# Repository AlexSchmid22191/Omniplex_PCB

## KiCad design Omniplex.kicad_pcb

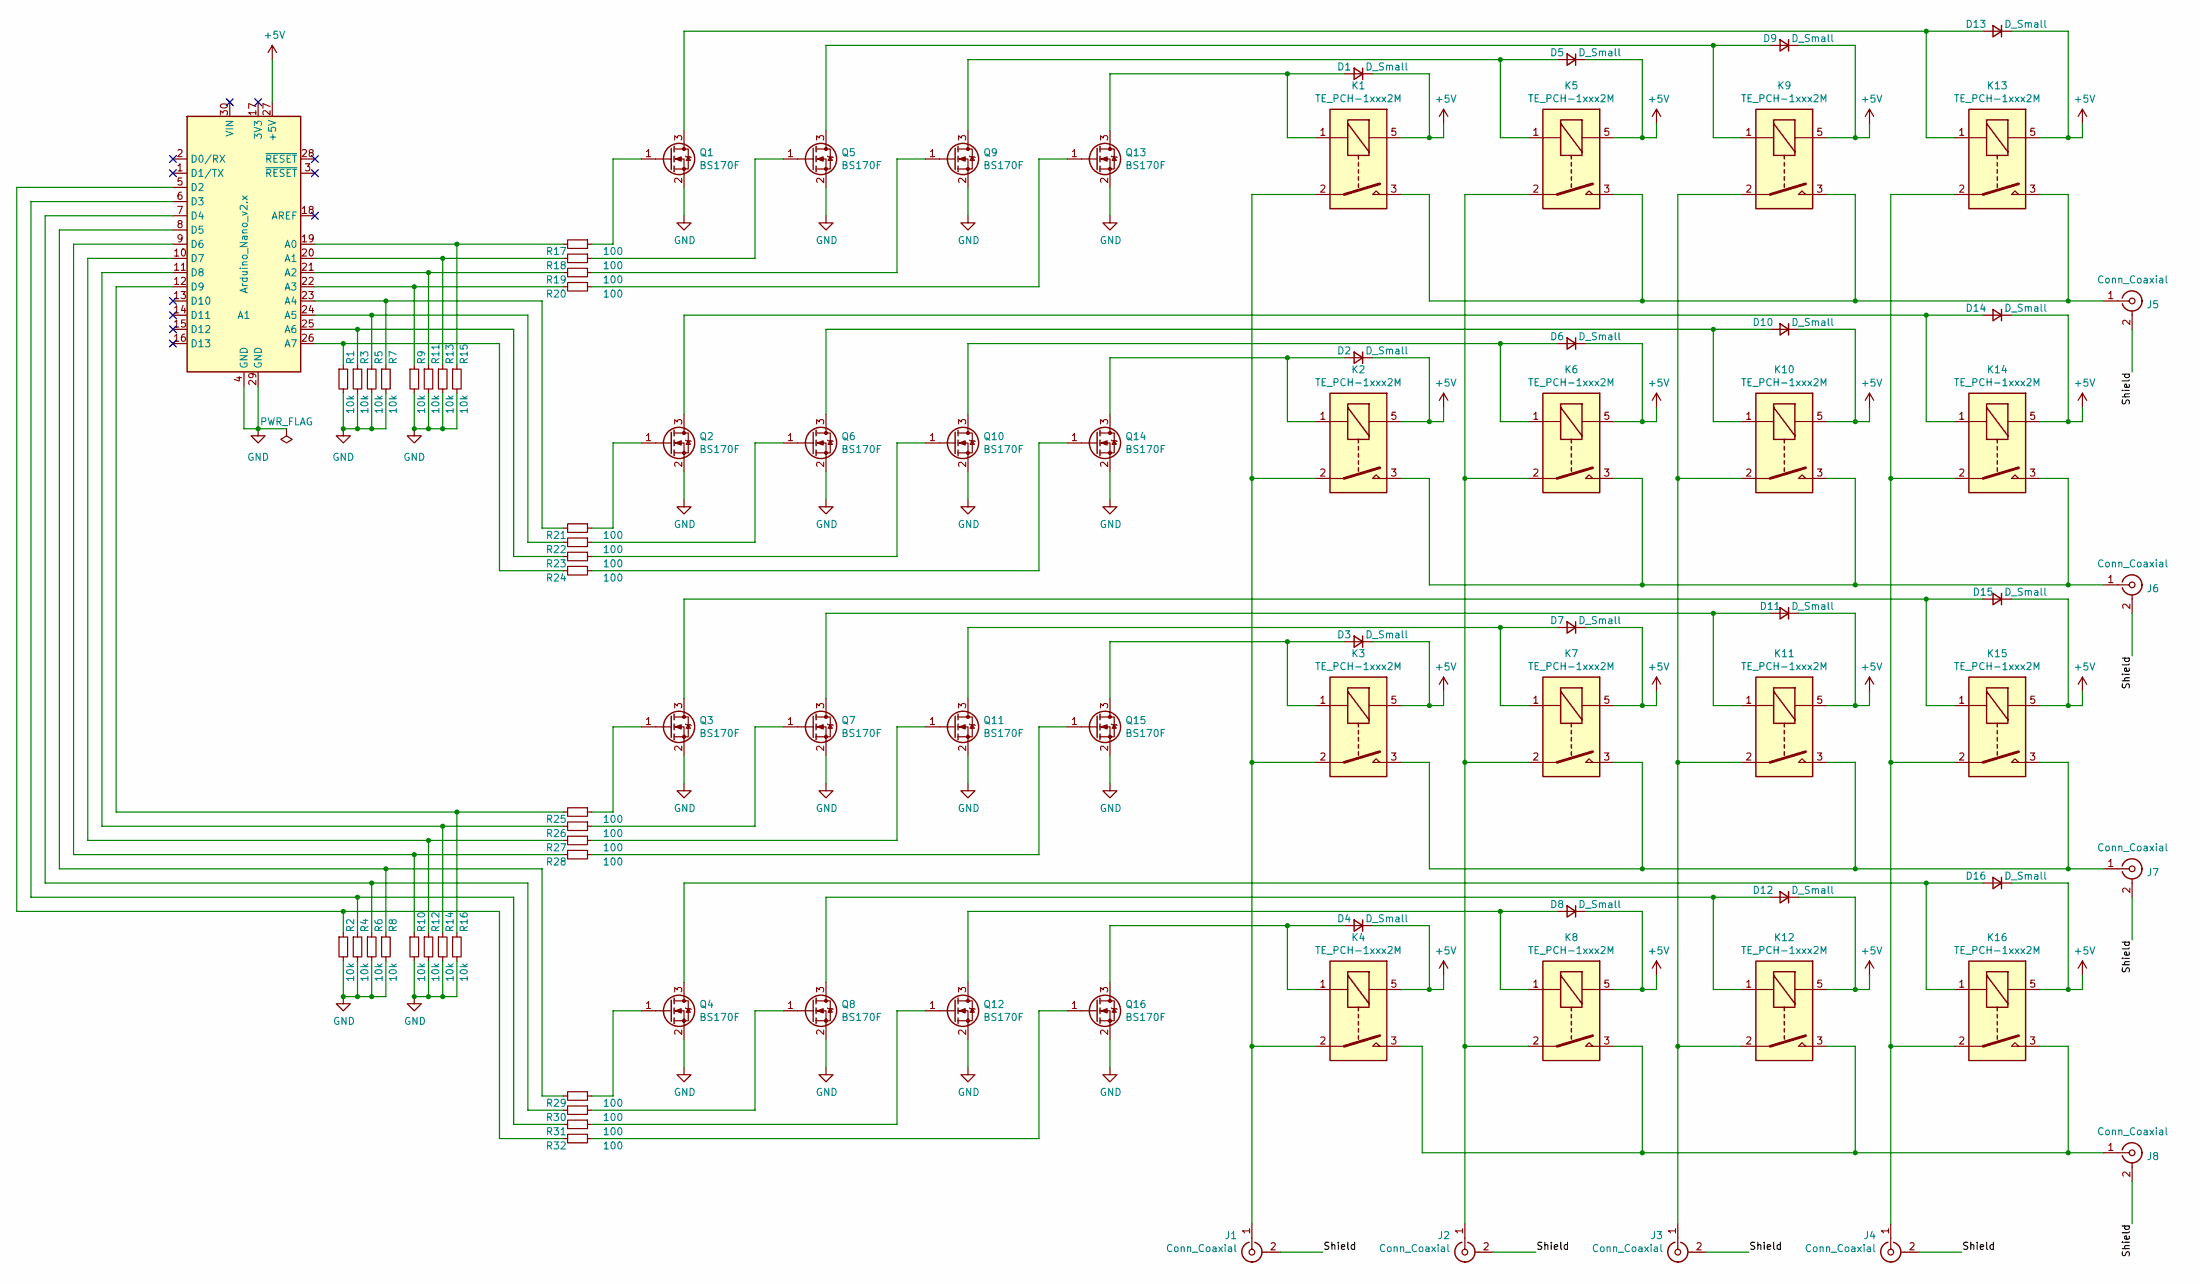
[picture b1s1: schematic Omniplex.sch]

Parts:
A1: Arduino_Nano_v2.x; Arduino_Nano
D1, D2, D3, D4, D5, D6, D7, D8, D9, D10, D11, D12, D13, D14, D15, D16: D_Small; D_0603_1608Metric_Pad1.05x0.95mm_HandSolder
J1, J2, J3, J4, J5, J6, J7, J8: Conn_Coaxial; BNC_Amphenol_B6252HB-NPP3G-50_Horizontal
K1, K2, K3, K4, K5, K6, K7, K8, K9, K10, K11, K12, K13, K14, K15, K16: TE_PCH-1xxx2M; Relay_SPST_TE_PCN-1xxD3MHZ_Mod
Q1, Q2, Q3, Q4, Q5, Q6, Q7, Q8, Q9, Q10, Q11, Q12, Q13, Q14, Q15, Q16: BS170F; SOT-23
R1, R2, R3, R4, R5, R6, R7, R8, R9, R10, R11, R12, R13, R14, R15, R16: 10k; R_0603_1608Metric_Pad1.05x0.95mm_HandSolder
R17, R18, R19, R20, R21, R22, R23, R24, R25, R26, R27, R28, R29, R30, R31, R32: 100; R_0603_1608Metric_Pad1.05x0.95mm_HandSolder

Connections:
+5V: A1.27 (+5V), D1.1 (K), D2.1 (K), D3.1 (K), D4.1 (K), D5.1 (K), D6.1 (K), D7.1 (K), D8.1 (K), D9.1 (K), D10.1 (K), D11.1 (K), D12.1 (K), D13.1 (K), D14.1 (K), D15.1 (K), D16.1 (K), K1.5, K2.5, K3.5, K4.5, K5.5, K6.5, K7.5, K8.5, K9.5, K10.5, K11.5, K12.5, K13.5, K14.5, K15.5, K16.5
/Shield: J1.2 (Ext), J2.2 (Ext), J3.2 (Ext), J4.2 (Ext), J5.2 (Ext), J6.2 (Ext), J7.2 (Ext), J8.2 (Ext)
GND: A1.4 (GND), A1.29 (GND), Q1.2 (S), Q2.2 (S), Q3.2 (S), Q4.2 (S), Q5.2 (S), Q6.2 (S), Q7.2 (S), Q8.2 (S), Q9.2 (S), Q10.2 (S), Q11.2 (S), Q12.2 (S), Q13.2 (S), Q14.2 (S), Q15.2 (S), Q16.2 (S), R1.2, R2.2, R3.2, R4.2, R5.2, R6.2, R7.2, R8.2, R9.2, R10.2, R11.2, R12.2, R13.2, R14.2, R15.2, R16.2
unnamed: A1.5 (D2), R2.1, R32.2
unnamed: A1.6 (D3), R4.1, R31.2
unnamed: A1.7 (D4), R6.1, R30.2
unnamed: A1.8 (D5), R8.1, R29.2
unnamed: A1.9 (D6), R10.1, R28.2
unnamed: A1.10 (D7), R12.1, R27.2
unnamed: A1.11 (D8), R14.1, R26.2
unnamed: A1.12 (D9), R16.1, R25.2
unnamed: A1.19 (A0), R15.1, R17.2
unnamed: A1.20 (A1), R13.1, R18.2
unnamed: A1.21 (A2), R11.1, R19.2
unnamed: A1.22 (A3), R9.1, R20.2
unnamed: A1.23 (A4), R7.1, R21.2
unnamed: A1.24 (A5), R5.1, R22.2
unnamed: A1.25 (A6), R3.1, R23.2
unnamed: A1.26 (A7), R1.1, R24.2
unnamed: D1.2 (A), K1.1, Q13.3 (D)
unnamed: D2.2 (A), K2.1, Q14.3 (D)
unnamed: D3.2 (A), K3.1, Q15.3 (D)
unnamed: D4.2 (A), K4.1, Q16.3 (D)
unnamed: D5.2 (A), K5.1, Q9.3 (D)
unnamed: D6.2 (A), K6.1, Q10.3 (D)
unnamed: D7.2 (A), K7.1, Q11.3 (D)
unnamed: D8.2 (A), K8.1, Q12.3 (D)
unnamed: D9.2 (A), K9.1, Q5.3 (D)
unnamed: D10.2 (A), K10.1, Q6.3 (D)
unnamed: D11.2 (A), K11.1, Q7.3 (D)
unnamed: D12.2 (A), K12.1, Q8.3 (D)
unnamed: D13.2 (A), K13.1, Q1.3 (D)
unnamed: D14.2 (A), K14.1, Q2.3 (D)
unnamed: D15.2 (A), K15.1, Q3.3 (D)
unnamed: D16.2 (A), K16.1, Q4.3 (D)
unnamed: J1.1 (In), K1.2, K2.2, K3.2, K4.2
unnamed: J2.1 (In), K5.2, K6.2, K7.2, K8.2
unnamed: J3.1 (In), K9.2, K10.2, K11.2, K12.2
unnamed: J4.1 (In), K13.2, K14.2, K15.2, K16.2
unnamed: J5.1 (In), K1.3, K5.3, K9.3, K13.3
unnamed: J6.1 (In), K2.3, K6.3, K10.3, K14.3
unnamed: J7.1 (In), K3.3, K7.3, K11.3, K15.3
unnamed: J8.1 (In), K4.3, K8.3, K12.3, K16.3
unnamed: Q1.1 (G), R17.1
unnamed: Q2.1 (G), R21.1
unnamed: Q3.1 (G), R25.1
unnamed: Q4.1 (G), R29.1
unnamed: Q5.1 (G), R18.1
unnamed: Q6.1 (G), R22.1
unnamed: Q7.1 (G), R26.1
unnamed: Q8.1 (G), R30.1
unnamed: Q9.1 (G), R19.1
unnamed: Q10.1 (G), R23.1
unnamed: Q11.1 (G), R27.1
unnamed: Q12.1 (G), R31.1
unnamed: Q13.1 (G), R20.1
unnamed: Q14.1 (G), R24.1
unnamed: Q15.1 (G), R28.1
unnamed: Q16.1 (G), R32.1

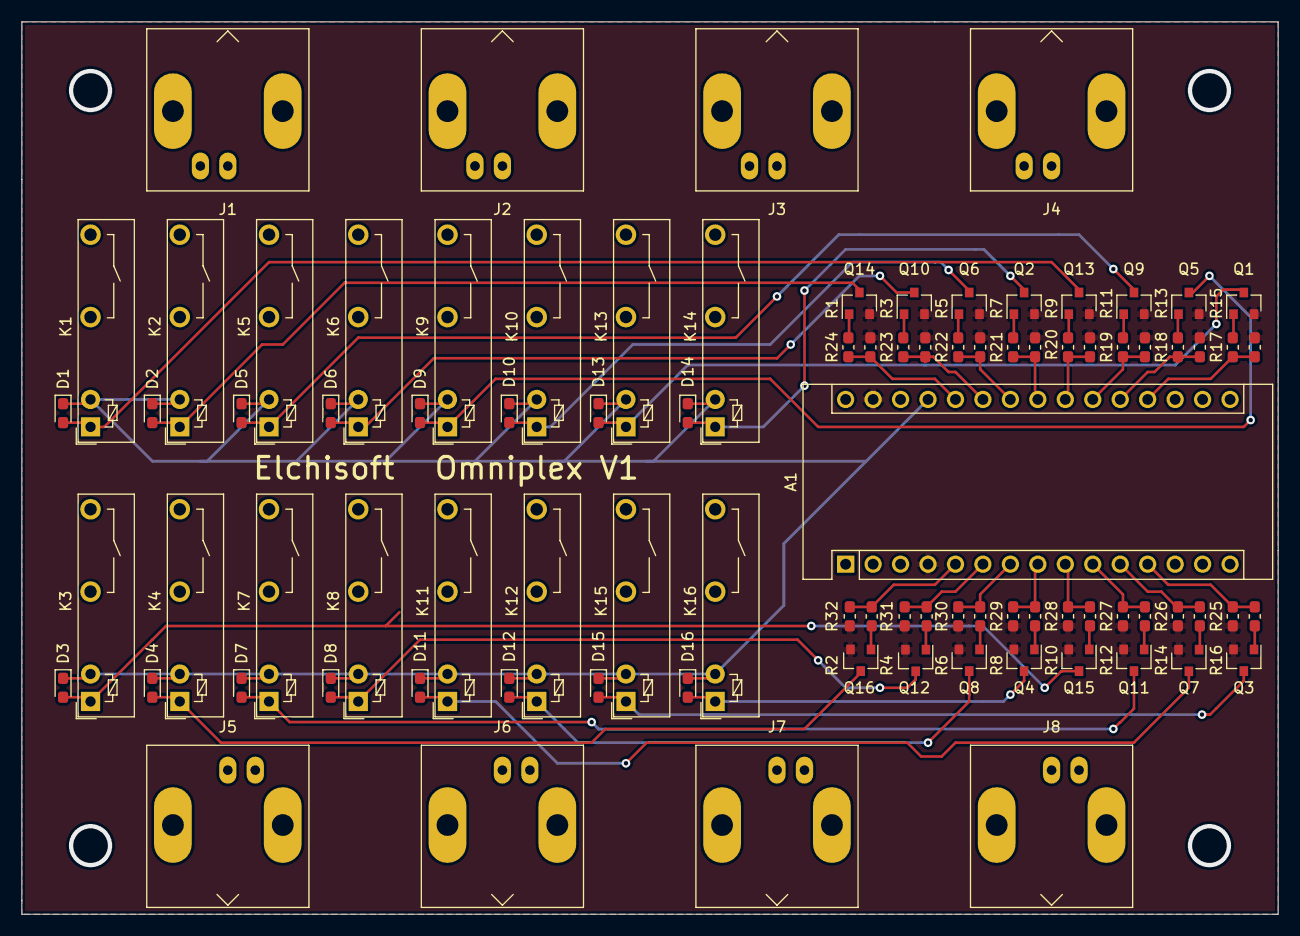
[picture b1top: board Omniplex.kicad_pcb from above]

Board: 4 copper layers, 116.2 x 82.6 mm, 89 parts (0 on the bottom side), 59 nets.

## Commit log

2022-02-01 initial
2022-02-01 asdf
